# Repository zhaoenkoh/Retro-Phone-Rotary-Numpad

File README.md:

# Retro Phone Rotary Numpad
A project just for laughs and as a present for one of my good friend. 
Retrofitting a retro phone to make it function as a number pad on the condition that all the number keys are rotary encoders and user.

Still in progress.

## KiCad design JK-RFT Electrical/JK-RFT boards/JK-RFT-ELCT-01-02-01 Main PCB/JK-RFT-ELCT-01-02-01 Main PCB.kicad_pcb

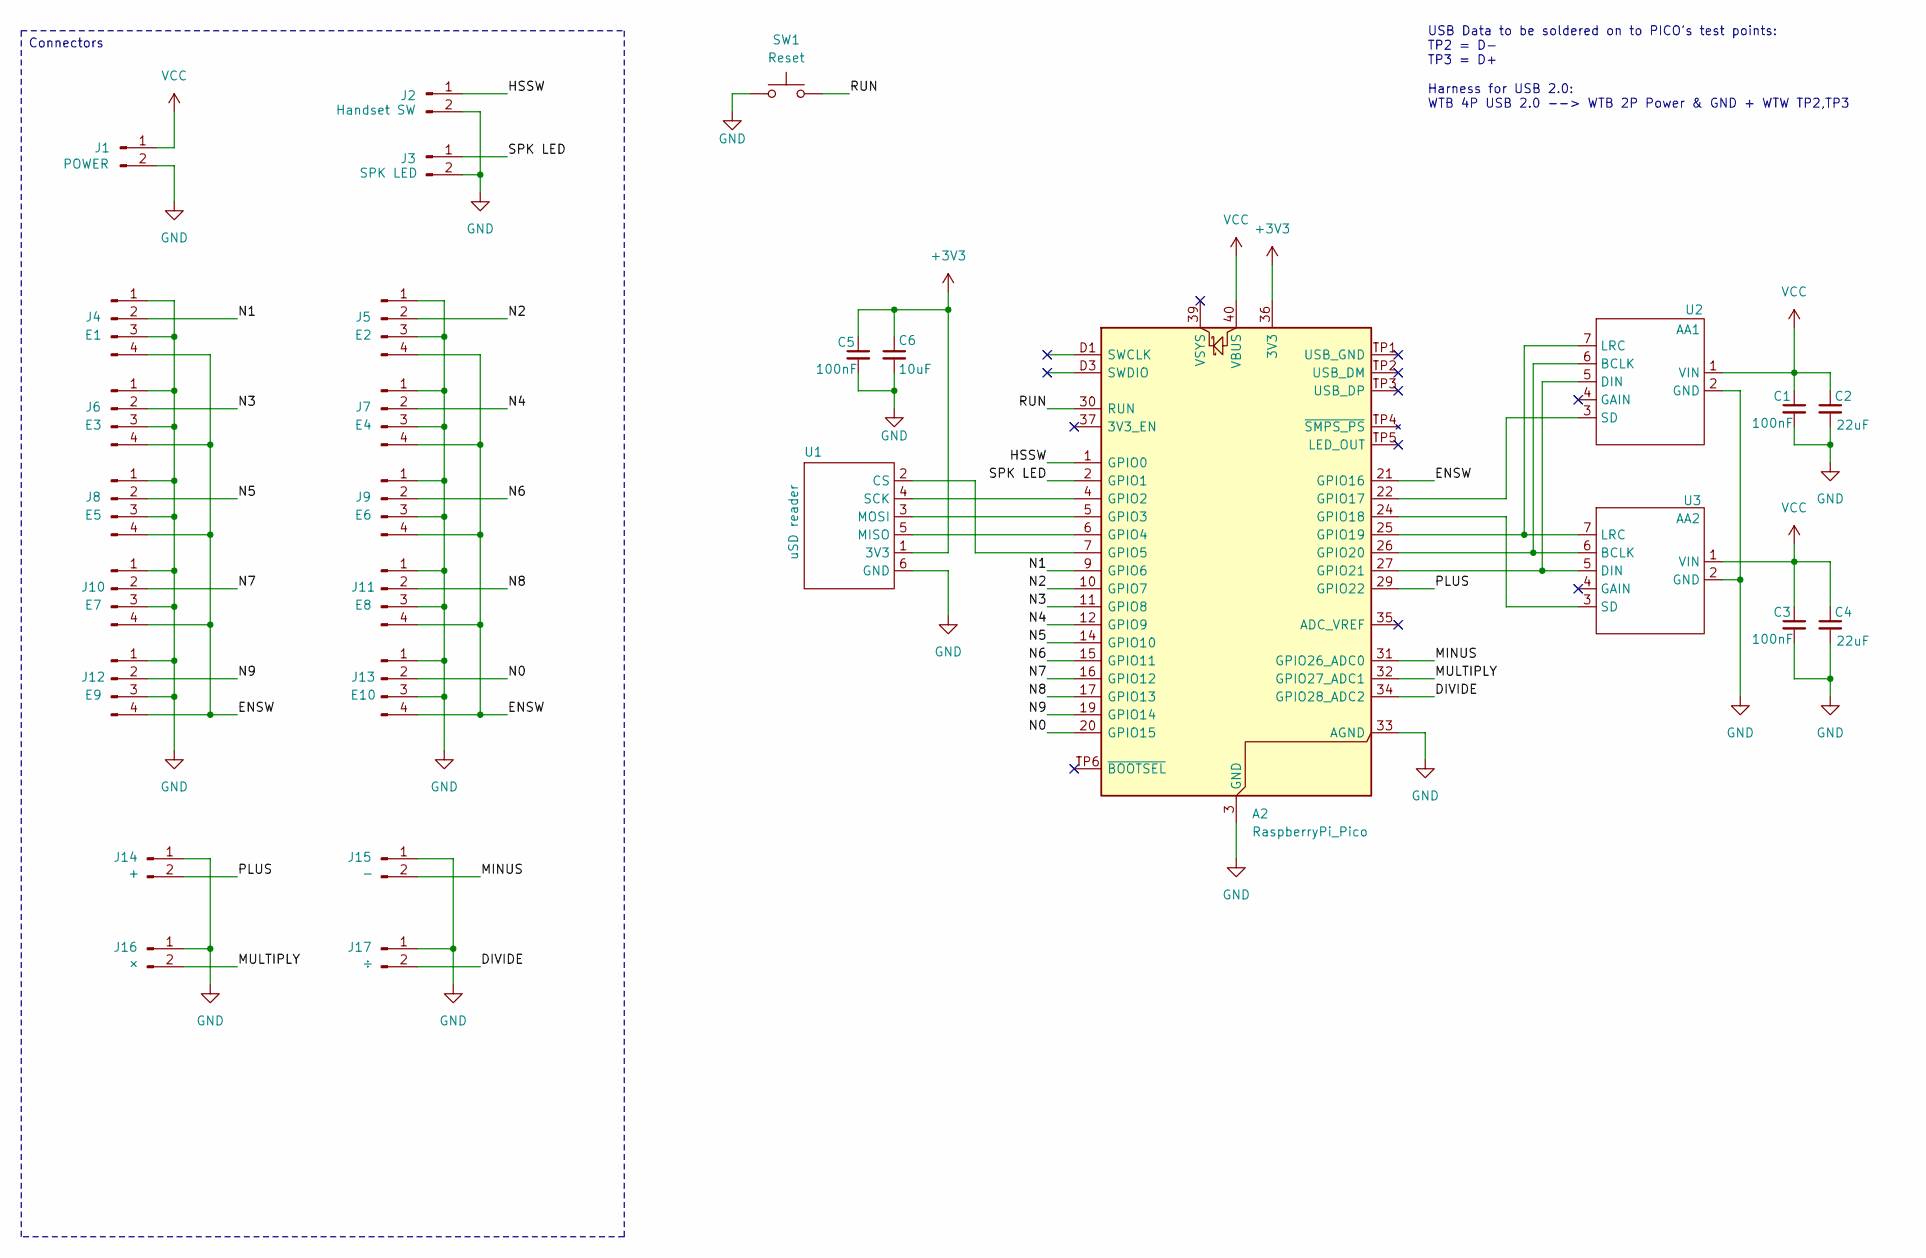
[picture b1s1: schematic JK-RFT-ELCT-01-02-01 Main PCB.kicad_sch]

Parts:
A2: RaspberryPi_Pico; RaspberryPi_Pico_Common_THT
C1, C3, C5: 100nF; C_0603_1608Metric_Pad1.08x0.95mm_HandSolder
C2, C4: 22uF; C_0805_2012Metric_Pad1.18x1.45mm_HandSolder
C6: 10uF; C_0805_2012Metric_Pad1.18x1.45mm_HandSolder
J1: POWER; JST_XH_B2B-XH-A_1x02_P2.50mm_Vertical
J2: Handset SW; JST_XH_B2B-XH-A_1x02_P2.50mm_Vertical
J3: SPK LED; JST_XH_B2B-XH-A_1x02_P2.50mm_Vertical
J4: E1; JST_XH_B4B-XH-A_1x04_P2.50mm_Vertical
J5: E2; JST_XH_B4B-XH-A_1x04_P2.50mm_Vertical
J6: E3; JST_XH_B4B-XH-A_1x04_P2.50mm_Vertical
J7: E4; JST_XH_B4B-XH-A_1x04_P2.50mm_Vertical
J8: E5; JST_XH_B4B-XH-A_1x04_P2.50mm_Vertical
J9: E6; JST_XH_B4B-XH-A_1x04_P2.50mm_Vertical
J10: E7; JST_XH_B4B-XH-A_1x04_P2.50mm_Vertical
J11: E8; JST_XH_B4B-XH-A_1x04_P2.50mm_Vertical
J12: E9; JST_XH_B4B-XH-A_1x04_P2.50mm_Vertical
J13: E10; JST_XH_B4B-XH-A_1x04_P2.50mm_Vertical
J14: +; JST_XH_B2B-XH-A_1x02_P2.50mm_Vertical
J15: -; JST_XH_B2B-XH-A_1x02_P2.50mm_Vertical
J16: ×; JST_XH_B2B-XH-A_1x02_P2.50mm_Vertical
J17: ÷; JST_XH_B2B-XH-A_1x02_P2.50mm_Vertical
SW1: Reset; SW_PUSH_6mm
U1: uSD reader; PinHeader_1x06_P2.54mm_Vertical
U2: AA1; MODULE_3006
U3: AA2; MODULE_3006

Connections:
+3V3: A2.36 (3V3), C5.1, C6.1, U1.1 (3V3)
/DIVIDE: A2.34 (GPIO28_ADC2), J17.2
/ENSW: A2.21 (GPIO16), J4.4, J5.4, J6.4, J7.4, J8.4, J9.4, J10.4, J11.4, J12.4, J13.4
/HSSW: A2.1 (GPIO0), J2.1
/MINUS: A2.31 (GPIO26_ADC0), J15.2
/MULTIPLY: A2.32 (GPIO27_ADC1), J16.2
/N0: A2.20 (GPIO15), J13.2
/N1: A2.9 (GPIO6), J4.2
/N2: A2.10 (GPIO7), J5.2
/N3: A2.11 (GPIO8), J6.2
/N4: A2.12 (GPIO9), J7.2
/N5: A2.14 (GPIO10), J8.2
/N6: A2.15 (GPIO11), J9.2
/N7: A2.16 (GPIO12), J10.2
/N8: A2.17 (GPIO13), J11.2
/N9: A2.19 (GPIO14), J12.2
/PLUS: A2.29 (GPIO22), J14.2
/RUN: A2.30 (RUN), SW1.2
/SPK LED: A2.2 (GPIO1), J3.1
GND: A2.3 (GND), A2.8 (GND), A2.13 (GND), A2.18 (GND), A2.23 (GND), A2.28 (GND), A2.33 (AGND), A2.38 (GND), A2.D2 (GND), C1.2, C2.2, C3.2, C4.2, C5.2, C6.2, J1.2, J2.2, J3.2, J4.1, J4.3, J5.1, J5.3, J6.1, J6.3, J7.1, J7.3, J8.1, J8.3, J9.1, J9.3, J10.1, J10.3, J11.1, J11.3, J12.1, J12.3, J13.1, J13.3, J14.1, J15.1, J16.1, J17.1, SW1.1, U1.6 (GND), U2.2 (GND), U3.2 (GND)
unnamed: A2.4 (GPIO2), U1.4 (SCK)
unnamed: A2.5 (GPIO3), U1.3 (MOSI)
unnamed: A2.6 (GPIO4), U1.5 (MISO)
unnamed: A2.7 (GPIO5), U1.2 (CS)
unnamed: A2.22 (GPIO17), U2.3 (SD)
unnamed: A2.24 (GPIO18), U3.3 (SD)
unnamed: A2.25 (GPIO19), U2.7 (LRC), U3.7 (LRC)
unnamed: A2.26 (GPIO20), U2.6 (BCLK), U3.6 (BCLK)
unnamed: A2.27 (GPIO21), U2.5 (DIN), U3.5 (DIN)
VCC: A2.40 (VBUS), C1.1, C2.1, C3.1, C4.1, J1.1, U2.1 (VIN), U3.1 (VIN)

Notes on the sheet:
USB Data to be soldered on to PICO's test points: TP2 = D- TP3 = D+ Harness for USB 2.0: WTB 4P USB 2.0 --> WTB 2P Power & GND + WTW TP2,TP3
Connectors

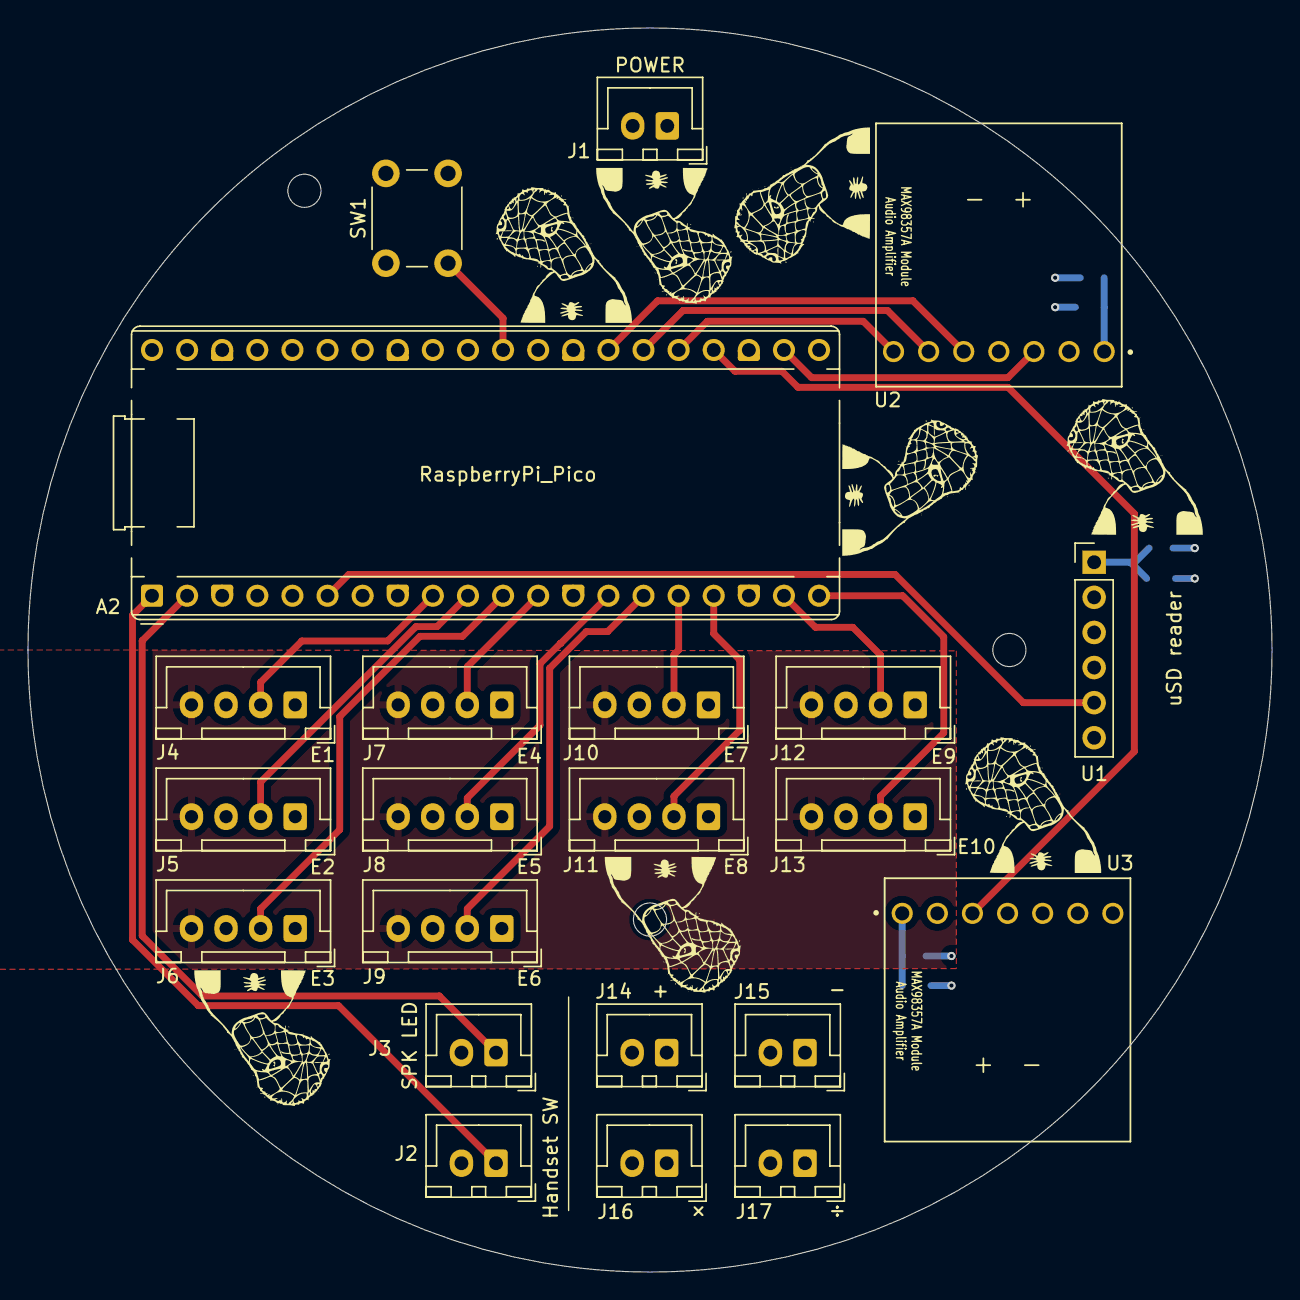
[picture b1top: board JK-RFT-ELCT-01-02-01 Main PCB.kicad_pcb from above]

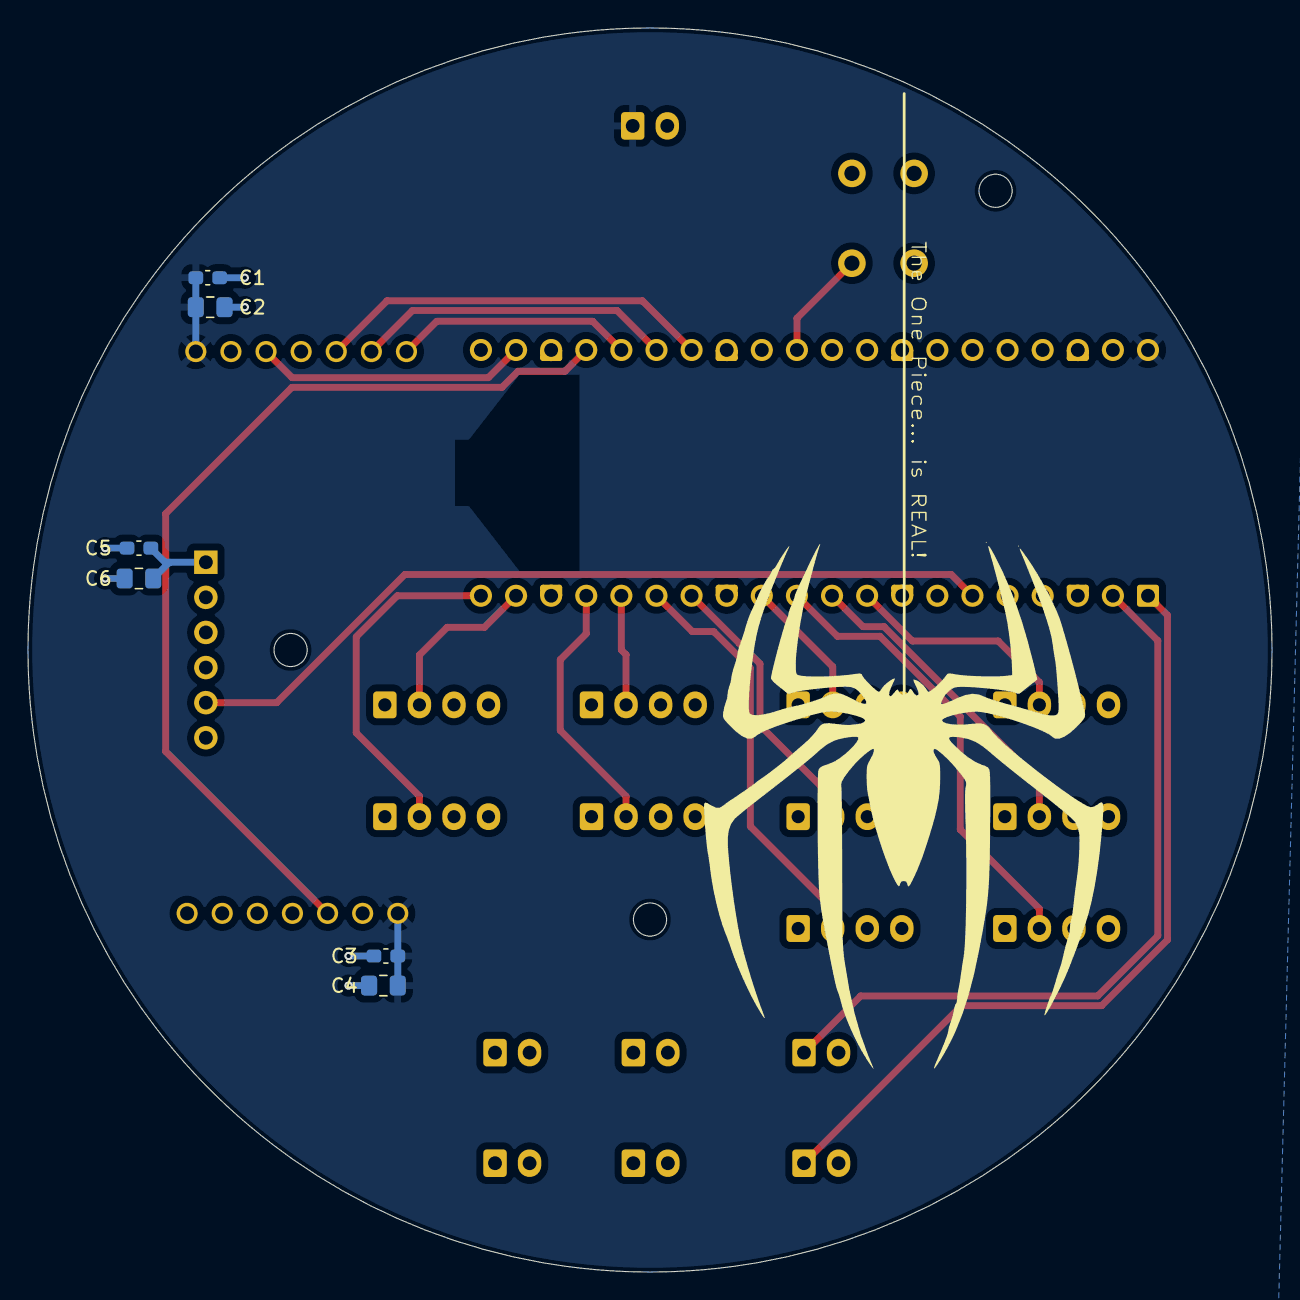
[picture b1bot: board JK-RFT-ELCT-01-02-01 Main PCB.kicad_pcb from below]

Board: 4 copper layers, 90.0 x 90.0 mm, 28 parts (6 on the bottom side), 30 nets.

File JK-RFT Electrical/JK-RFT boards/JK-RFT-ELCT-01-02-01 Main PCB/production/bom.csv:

Designator,Footprint,Quantity,Value,LCSC Part #
A2,RaspberryPi_Pico_Common_THT,1,RaspberryPi_Pico,
"C1, C3, C5",0603,3,100nF,
"C2, C4",0805,2,22uF,
C6,0805,1,10uF,
J1,JST_XH_B2B-XH-A_1x02_P2.50mm_Vertical,1,POWER,
J10,JST_XH_B4B-XH-A_1x04_P2.50mm_Vertical,1,E7,
J11,JST_XH_B4B-XH-A_1x04_P2.50mm_Vertical,1,E8,
J12,JST_XH_B4B-XH-A_1x04_P2.50mm_Vertical,1,E9,
J13,JST_XH_B4B-XH-A_1x04_P2.50mm_Vertical,1,E10,
J14,JST_XH_B2B-XH-A_1x02_P2.50mm_Vertical,1,+,
J15,JST_XH_B2B-XH-A_1x02_P2.50mm_Vertical,1,-,
J16,JST_XH_B2B-XH-A_1x02_P2.50mm_Vertical,1,×,
J17,JST_XH_B2B-XH-A_1x02_P2.50mm_Vertical,1,÷,
J2,JST_XH_B2B-XH-A_1x02_P2.50mm_Vertical,1,Handset SW,
J3,JST_XH_B2B-XH-A_1x02_P2.50mm_Vertical,1,SPK LED,
J4,JST_XH_B4B-XH-A_1x04_P2.50mm_Vertical,1,E1,
J5,JST_XH_B4B-XH-A_1x04_P2.50mm_Vertical,1,E2,
J6,JST_XH_B4B-XH-A_1x04_P2.50mm_Vertical,1,E3,
J7,JST_XH_B4B-XH-A_1x04_P2.50mm_Vertical,1,E4,
J8,JST_XH_B4B-XH-A_1x04_P2.50mm_Vertical,1,E5,
J9,JST_XH_B4B-XH-A_1x04_P2.50mm_Vertical,1,E6,
SW1,SW_PUSH_6mm,1,Reset,
U1,PinHeader_1x06_P2.54mm_Vertical,1,uSD reader,
U2,MODULE_3006,1,AA1,
U3,MODULE_3006,1,AA2,

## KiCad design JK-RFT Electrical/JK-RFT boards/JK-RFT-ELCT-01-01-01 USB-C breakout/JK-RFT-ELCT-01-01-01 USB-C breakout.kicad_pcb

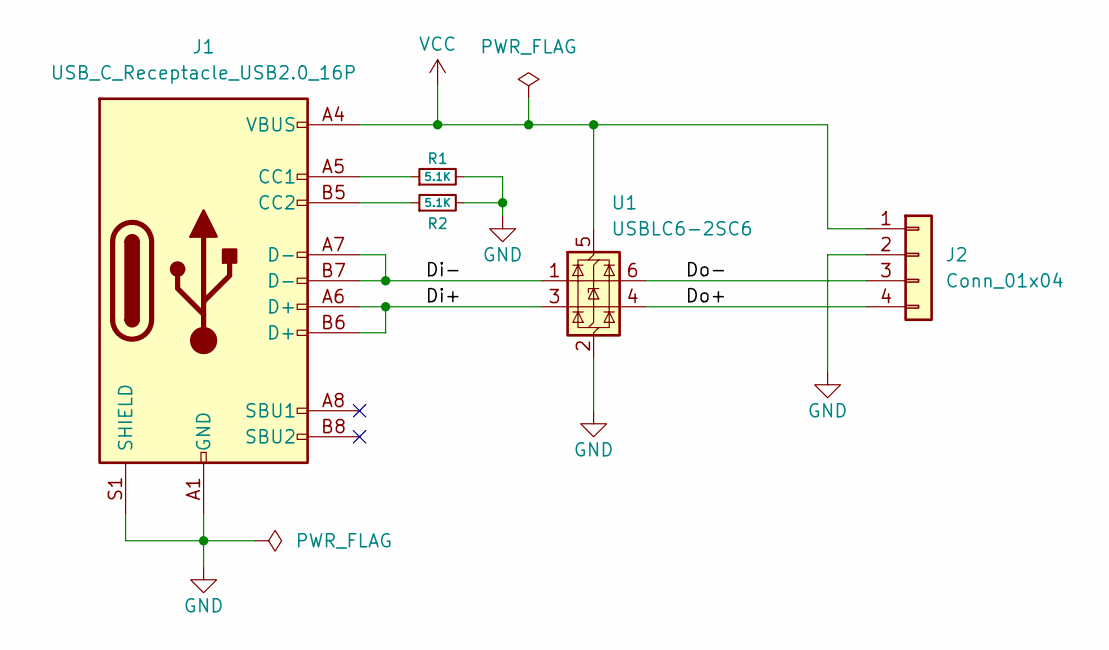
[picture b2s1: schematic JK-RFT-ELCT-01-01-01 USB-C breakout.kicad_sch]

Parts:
J1: USB_C_Receptacle_USB2.0_16P; USB_C_Receptacle_HCTL_HC-TYPE-C-16P-01A
J2: Conn_01x04; JST_XH_B4B-XH-AM_1x04_P2.50mm_Vertical
R1, R2: 5.1K; R_0603_1608Metric_Pad0.98x0.95mm_HandSolder
U1: USBLC6-2SC6; SOT-23-6

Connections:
/Di+: J1.A6 (D+), J1.B6 (D+), U1.3 (I/O2)
/Di-: J1.A7 (D-), J1.B7 (D-), U1.1 (I/O1)
/Do+: J2.4, U1.4 (I/O2)
/Do-: J2.3, U1.6 (I/O1)
GND: J1.A1 (GND), J1.A12 (GND), J1.B1 (GND), J1.B12 (GND), J1.S1 (SHIELD), J2.2, R1.2, R2.2, U1.2 (GND)
unnamed: J1.A5 (CC1), R1.1
unnamed: J1.B5 (CC2), R2.1
VCC: J1.A4 (VBUS), J1.A9 (VBUS), J1.B4 (VBUS), J1.B9 (VBUS), J2.1, U1.5 (VBUS)

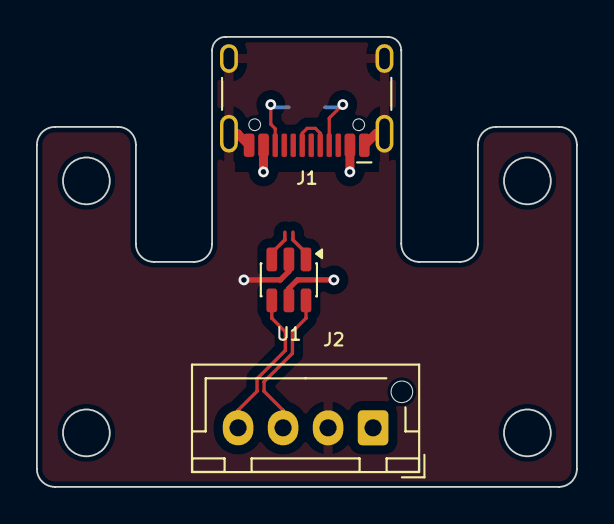
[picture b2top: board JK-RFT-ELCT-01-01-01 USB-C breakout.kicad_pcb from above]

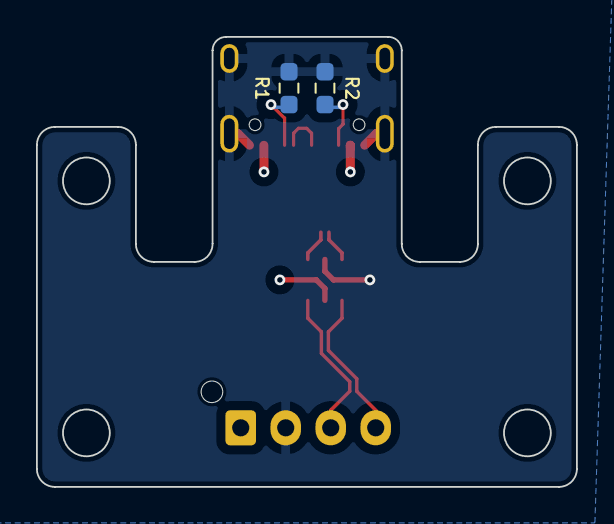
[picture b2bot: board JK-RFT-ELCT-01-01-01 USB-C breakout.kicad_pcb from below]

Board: 4 copper layers, 30.0 x 25.0 mm, 5 parts (2 on the bottom side), 8 nets.

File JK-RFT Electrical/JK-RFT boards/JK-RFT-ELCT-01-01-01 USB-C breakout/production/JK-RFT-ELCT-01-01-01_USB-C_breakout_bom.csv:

Designator,Footprint,Quantity,Value,LCSC Part #
J1,USB_C_Receptacle_HCTL_HC-TYPE-C-16P-01A,1,USB_C_Receptacle_USB2.0_16P,
J2,JST_XH_B4B-XH-AM_1x04_P2.50mm_Vertical,1,Conn_01x04,
"R1, R2",0603,2,5.1K,
U1,SOT-23-6,1,USBLC6-2SC6,
